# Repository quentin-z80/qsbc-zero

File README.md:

# qsbc-zero

## About

Specs:

- i.MX6ULL ARM Cortex-A7
- 512MB DDR3L
- 4MB QSPI Flash
- MicroSD card slot
- USB Type-C DRP and USB Type-A port
- 10/100M Ethernet
- Dual 36 pin GPIO headers
- PF1510 PMIC
- USB Type-C Power in

Manufactured using JLCPCB's JLC2116 stackup

## Setup

### Flashing u-boot

  1. Build `imx_usb_loader`

        ```
        git clone git@github.com:boundarydevices/imx_usb_loader.git
        cd imx_usb_loader
        make
        ```

  2. Build `u-boot`

        ```
        git clone git@gitlab.com:quentin-z80/u-boot.git
        cd u-boot
        export CROSS_COMPILE=arm-linux-gnueabi- ARCH=arm
        make qsbc-zero_defconfig
        make
        ```

  3. Build `qspi-header`

        ```
        cd tools/qspi-header
        ./qspi-header.sh qspi-nor-winbond-w25q32jv-config qspi-config.bin
        ```

  4. Connect to board over serial and load `u-boot` over usb

        ```
        screen /dev/ttyUSB0 115200
        ./imx_usb_loader /path/to/u-boot/u-boot-dtb.imx
        ```

  5. Transfer `qspi-header` over XMODEM or any other method and flash

        ```
        sf probe
        sf erase 0x0 0x400000
        loadx
        ```

        in screen hit `Ctrl-A` followed by `:`

        ```
        exec !! sx /path/to/qspi-header/qspi-config.bin
        sf write $loadaddr 0x400 $filesize
        ```

  6. Transfer `u-boot` over XMODEM or any other method and flash

        ```
        loadx
        ```

        in screen hit `Ctrl-A` followed by `:`

        ```
        exec !! sx /path/to/u-boot/u-boot-dtb.imx
        sf write $loadaddr 0x1000 $filesize
        ```

  7. Blow fuses to boot from qspi

        ```
        fuse prog -y 0 5 0x10 #BOOT_CFG1[4] = 1
        fuse prog -y 0 6 0x10 #BT_FUSE_SEL = 1
        ```

## TODO

### Rev 3
- Use interrupt for ETH PHY
- Swap USB-A and USB-C Locations
- Change SOC power tracks to zones

### Linux
- Port PF1510 driver

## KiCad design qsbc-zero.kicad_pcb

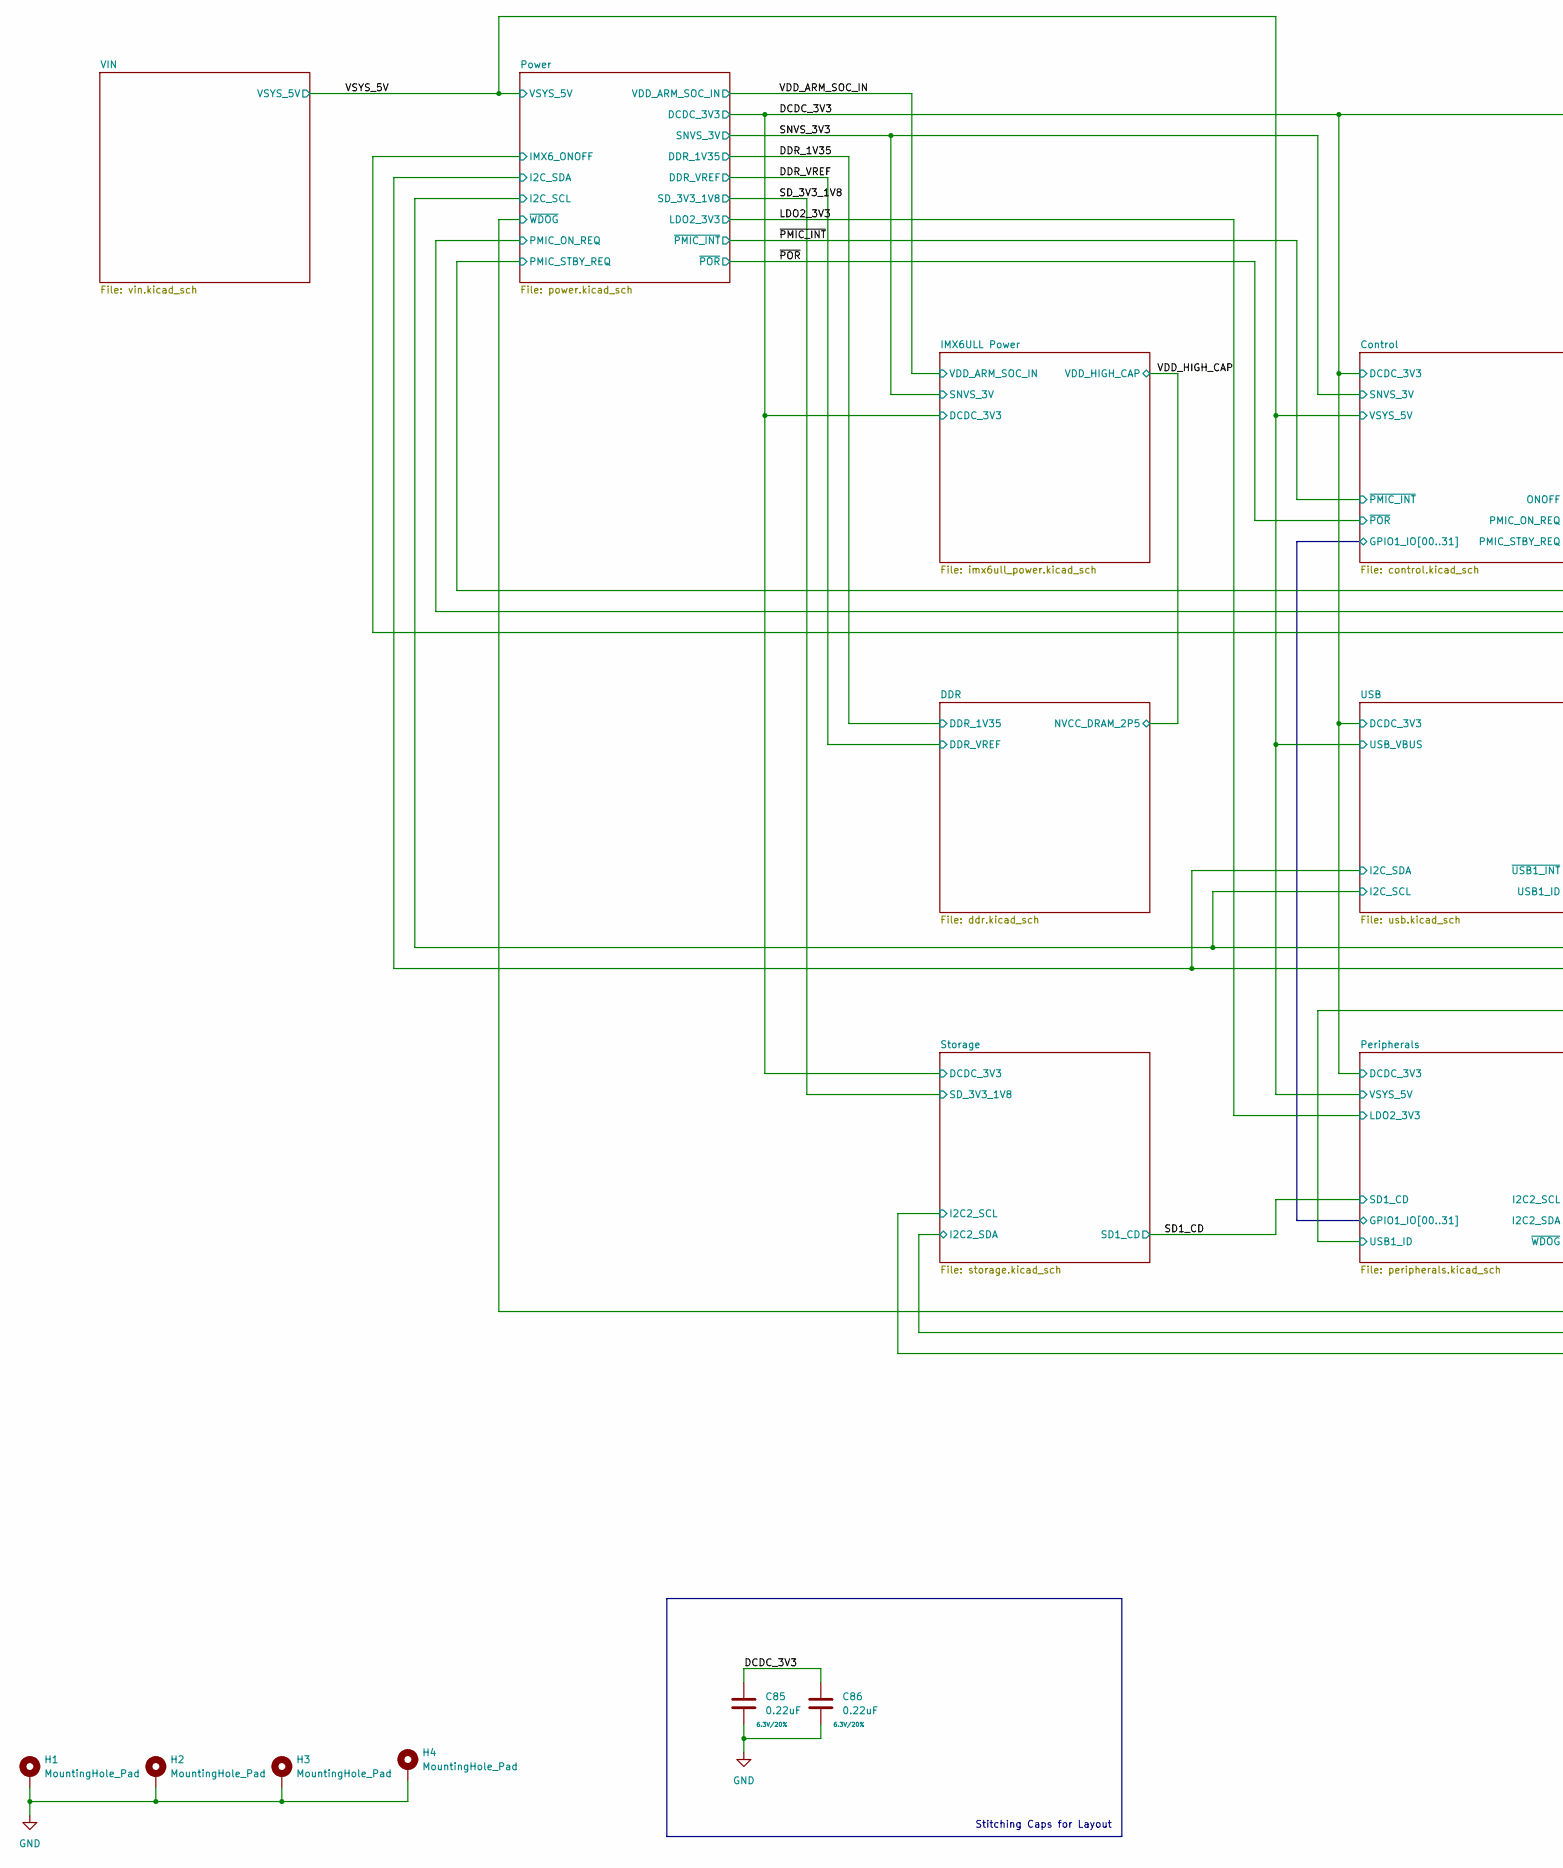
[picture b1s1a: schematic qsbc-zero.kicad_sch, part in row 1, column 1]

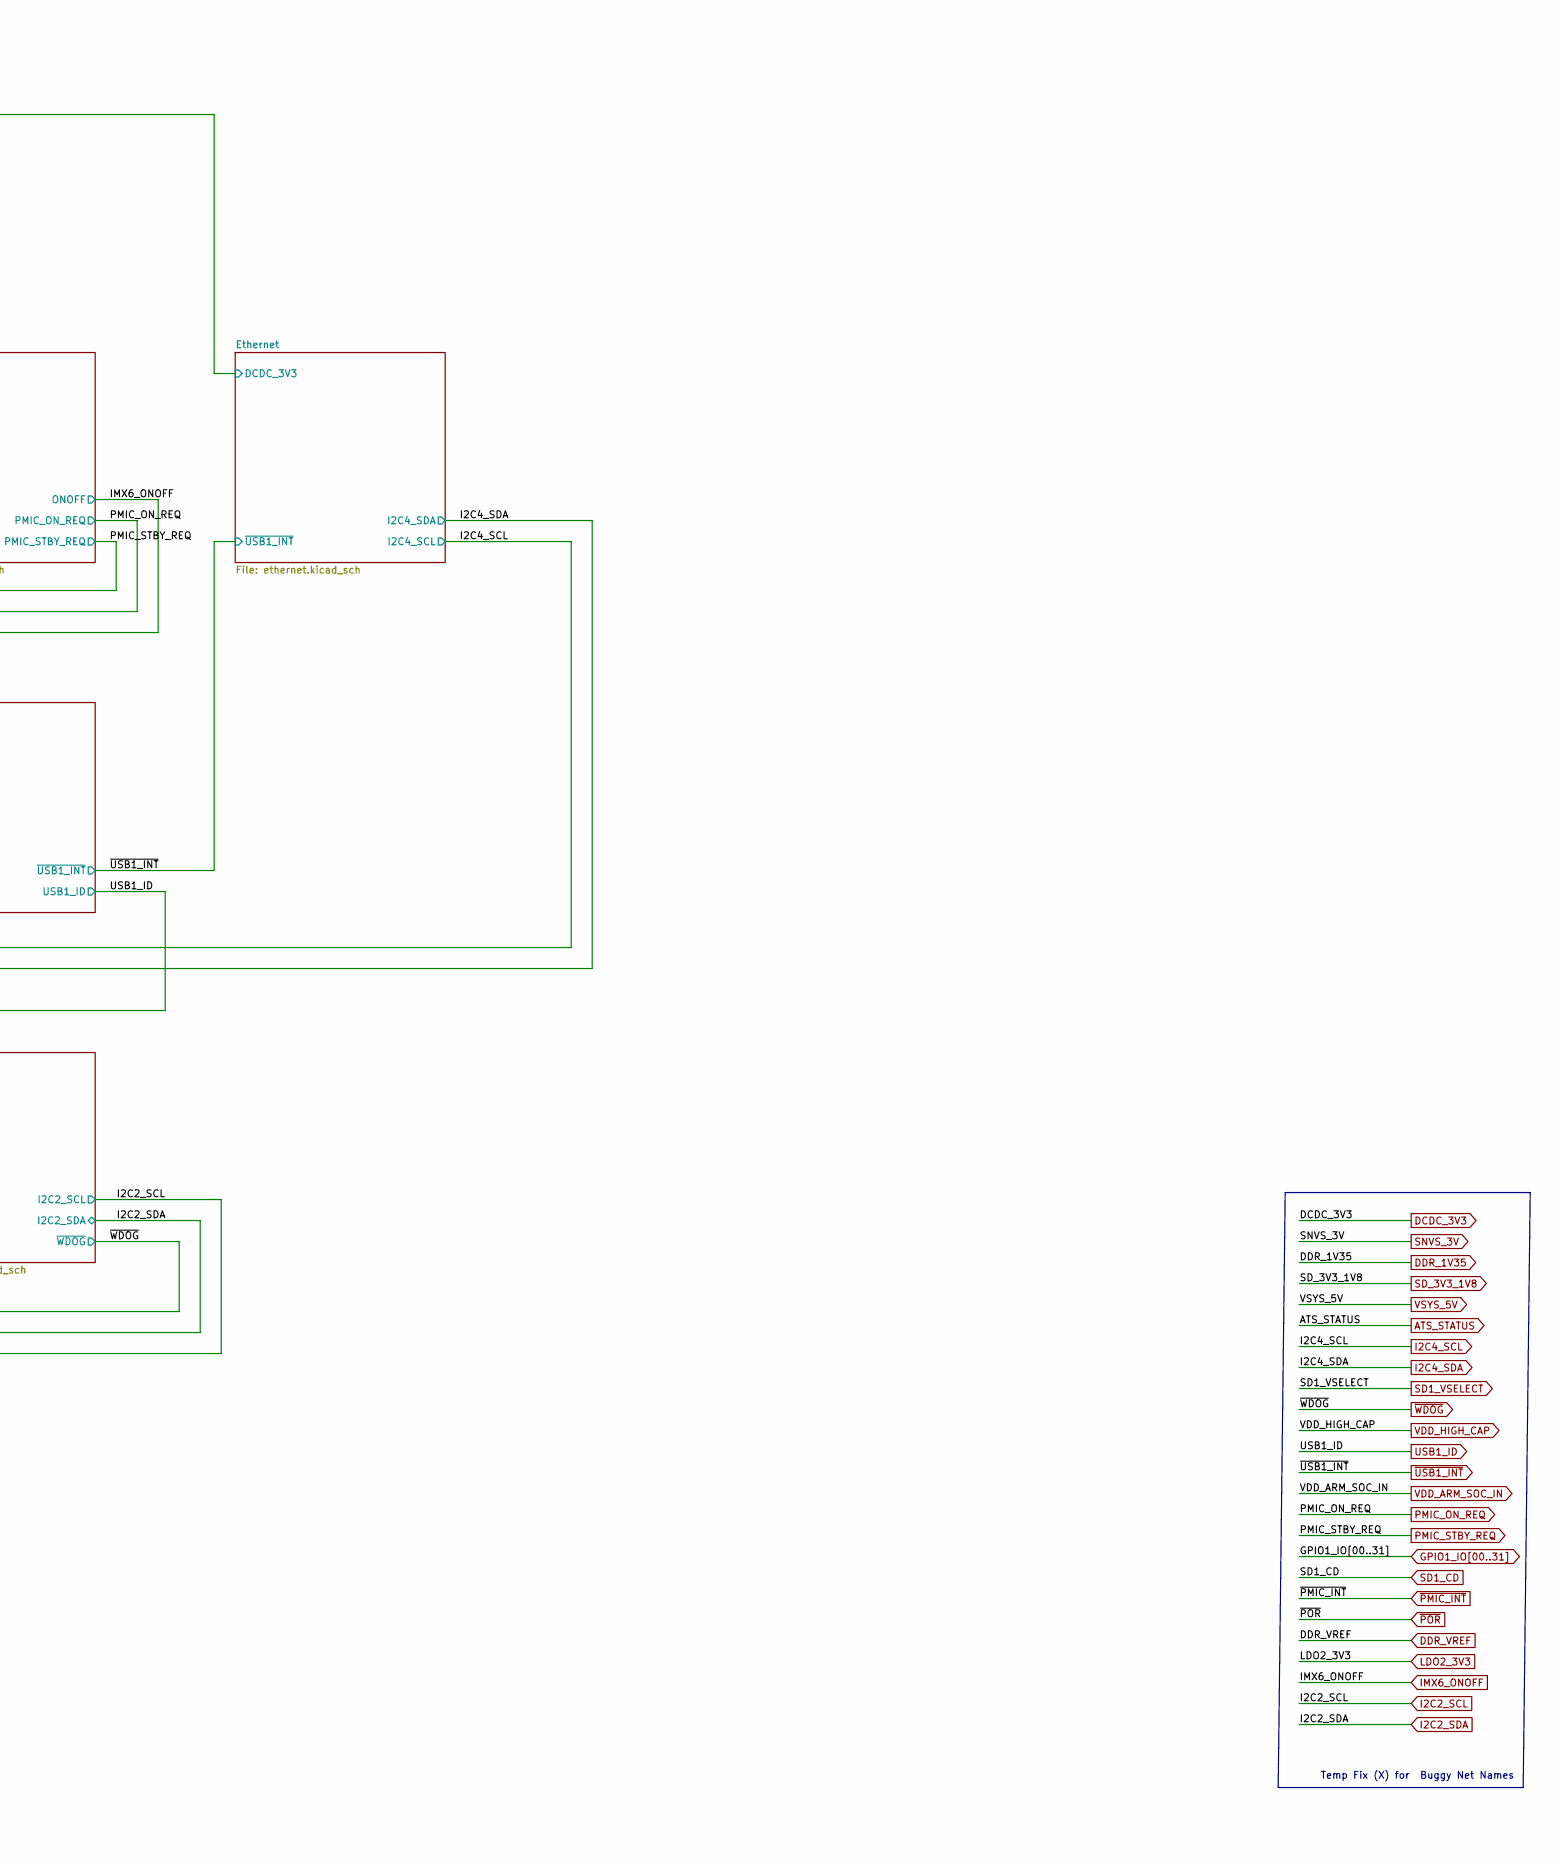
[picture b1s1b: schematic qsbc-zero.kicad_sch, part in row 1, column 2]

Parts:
C85, C86: 0.22uF; C_0201_0603Metric; Rating 6.3V/20%; MPN GRM033C80J224KE90D; DigiKey_PN 490-10392-1-ND
H1, H2, H3, H4: MountingHole_Pad; MountingHole_3.2mm_M3_Pad_Via

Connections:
DCDC_3V3: C85.1, C86.1; also elsewhere on the board
GND: C85.2, C86.2, H1.1, H2.1, H3.1, H4.1; also elsewhere on the board

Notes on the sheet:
Stitching Caps for Layout
Temp Fix (X) for Buggy Net Names

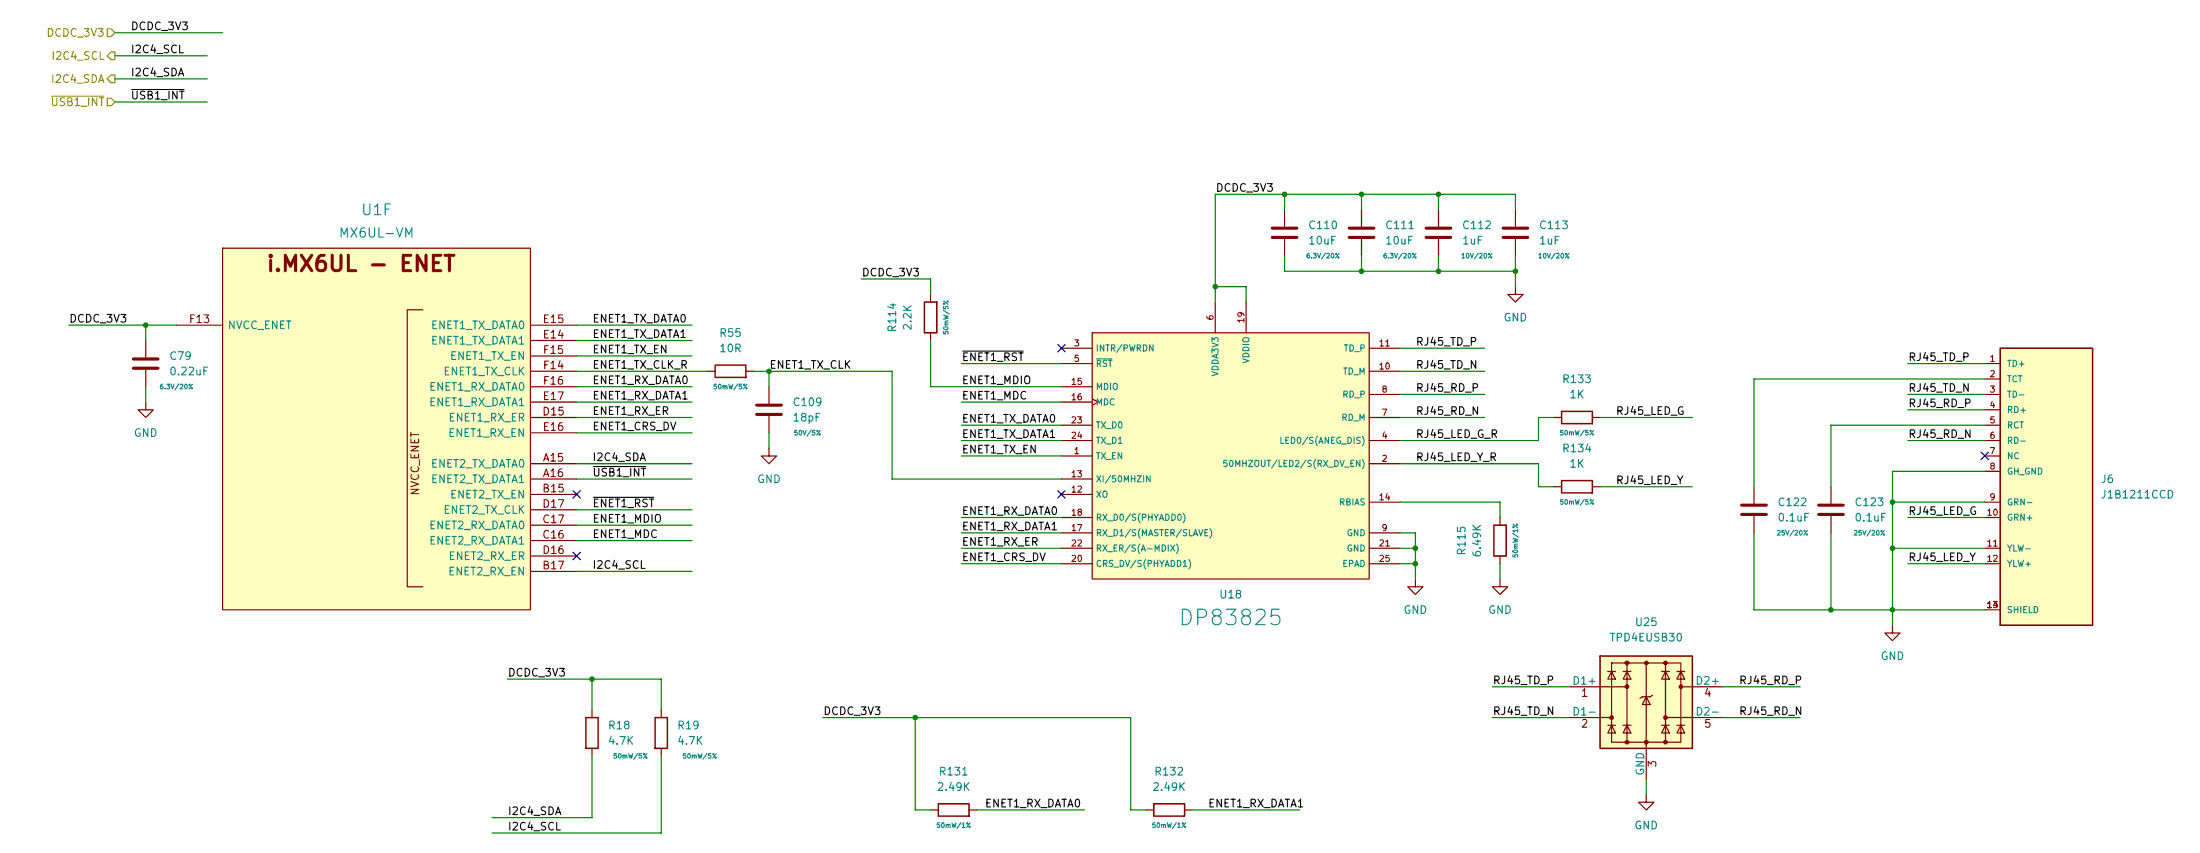
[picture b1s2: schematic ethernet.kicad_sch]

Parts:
C79: 0.22uF; C_0201_0603Metric; Rating 6.3V/20%; MPN GRM033C80J224KE90D; DigiKey_PN 490-10392-1-ND
C109: 18pF; C_0402_1005Metric; Rating 50V/5%; MPN CC0402JRNPO9BN180; DigiKey_PN 311-1415-1-ND
C110, C111: 10uF; C_0402_1005Metric; Rating 6.3V/20%; MPN GRM155R60J106ME05D; DigiKey_PN 490-GRM155R60J106ME05DCT-ND
C112, C113: 1uF; C_0402_1005Metric; Rating 10V/20%; MPN GCM155C71A105KE38D; DigiKey_PN 490-13409-1-ND
C122, C123: 0.1uF; C_0402_1005Metric; Rating 25V/20%; MPN GRM155R71E104KE14J; DigiKey_PN 490-14603-1-ND
J6: J1B1211CCD; MPN J1B1211CCD; DigiKey_PN 1278-1052-ND
R18, R19: 4.7K; R_0402_1005Metric; Rating 50mW/5%; MPN RC0402JR-074K7L; DigiKey_PN 311-4.7KJRCT-ND
R55: 10R; R_0402_1005Metric; Rating 50mW/5%; MPN RC0402JR-0710RL; DigiKey_PN 311-10JRCT-ND
R114: 2.2K; R_0402_1005Metric; Rating 50mW/5%; MPN RC0402JR-072K2L; DigiKey_PN 311-2.2KJRCT-ND
R115: 6.49K; R_0402_1005Metric; Rating 50mW/1%; MPN RC0402FR-076K49L; DigiKey_PN 311-6.49KLRCT-ND
R131, R132: 2.49K; R_0402_1005Metric; Rating 50mW/1%; MPN RC0402FR-072K49L; DigiKey_PN 311-2.49KLRCT-ND
R133, R134: 1K; R_0402_1005Metric; Rating 50mW/5%; MPN RC0402JR-071KL; DigiKey_PN 311-1.0KJRCT-ND
U1: MX6UL-VM; SOT1534-2; MPN MCIMX6Y2DVM09AB; DigiKey_PN 568-14995-ND
U18: DP83825; XCVR_DP83825IRMQR; MPN DP83825IRMQR; DigiKey_PN 296-DP83825IRMQRCT-ND
U25: TPD4EUSB30; USON-10_2.5x1.0mm_P0.5mm; MPN TPD4EUSB30DQAR; DigiKey_PN 296-28063-1-ND

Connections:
/Ethernet/ENET1_CRS_DV: U1.E16 (ENET1_RX_EN), U18.20 (CRS_DV/S(PHYADD1))
/Ethernet/ENET1_MDC: U1.C16 (ENET2_RX_DATA1), U18.16 (MDC)
/Ethernet/ENET1_MDIO: R114.1, U1.C17 (ENET2_RX_DATA0), U18.15 (MDIO)
/Ethernet/ENET1_RX_DATA0: R131.2, U1.F16 (ENET1_RX_DATA0), U18.18 (RX_D0/S(PHYADD0))
/Ethernet/ENET1_RX_DATA1: R132.2, U1.E17 (ENET1_RX_DATA1), U18.17 (RX_D1/S(MASTER/SLAVE))
/Ethernet/ENET1_RX_ER: U1.D15 (ENET1_RX_ER), U18.22 (RX_ER/S(A-MDIX))
/Ethernet/ENET1_TX_CLK: C109.1, R55.2, U18.13 (XI/50MHZIN)
/Ethernet/ENET1_TX_CLK_R: R55.1, U1.F14 (ENET1_TX_CLK)
/Ethernet/ENET1_TX_DATA0: U1.E15 (ENET1_TX_DATA0), U18.23 (TX_D0)
/Ethernet/ENET1_TX_DATA1: U1.E14 (ENET1_TX_DATA1), U18.24 (TX_D1)
/Ethernet/ENET1_TX_EN: U1.F15 (ENET1_TX_EN), U18.1 (TX_EN)
/Ethernet/RJ45_LED_G: J6.10 (GRN+), R133.2
/Ethernet/RJ45_LED_G_R: R133.1, U18.4 (LED0/S(ANEG_DIS))
/Ethernet/RJ45_LED_Y: J6.12 (YLW+), R134.2
/Ethernet/RJ45_LED_Y_R: R134.1, U18.2 (50MHZOUT/LED2/S(RX_DV_EN))
/Ethernet/RJ45_RD_N: J6.6 (RD-), U18.7 (RD_M), U25.5 (D2-), U25.6
/Ethernet/RJ45_RD_P: J6.4 (RD+), U18.8 (RD_P), U25.4 (D2+), U25.7
/Ethernet/RJ45_TD_N: J6.3 (TD-), U18.10 (TD_M), U25.2 (D1-), U25.9
/Ethernet/RJ45_TD_P: J6.1 (TD+), U18.11 (TD_P), U25.1 (D1+), U25.10
/Ethernet/~ENET1_RST: U1.D17 (ENET2_TX_CLK), U18.5 (~RST)
DCDC_3V3: C79.1, C110.1, C111.1, C112.1, C113.1, R18.1, R19.1, R114.2, R131.1, R132.1, U1.F13 (NVCC_ENET), U18.6 (VDDA3V3), U18.19 (VDDIO); also elsewhere on the board
GND: C79.2, C109.2, C110.2, C111.2, C112.2, C113.2, C122.2, C123.2, J6.8 (GH_GND), J6.9 (GRN-), J6.11 (YLW-), J6.13 (SHIELD), J6.14 (SHIELD), R115.1, U18.9 (GND), U18.21 (GND), U18.25 (EPAD), U18.26 (EPAD), U18.27 (EPAD), U18.28 (EPAD), U18.29 (EPAD), U18.30 (EPAD), U25.3 (GND), U25.8 (GND); also elsewhere on the board
I2C4_SCL: R19.2, U1.B17 (ENET2_RX_EN); also elsewhere on the board
I2C4_SDA: R18.2, U1.A15 (ENET2_TX_DATA0); also elsewhere on the board
unnamed: C122.1, J6.2 (TCT)
unnamed: C123.1, J6.5 (RCT)
unnamed: R115.2, U18.14 (RBIAS)
~USB1_INT: U1.A16 (ENET2_TX_DATA1); also elsewhere on the board

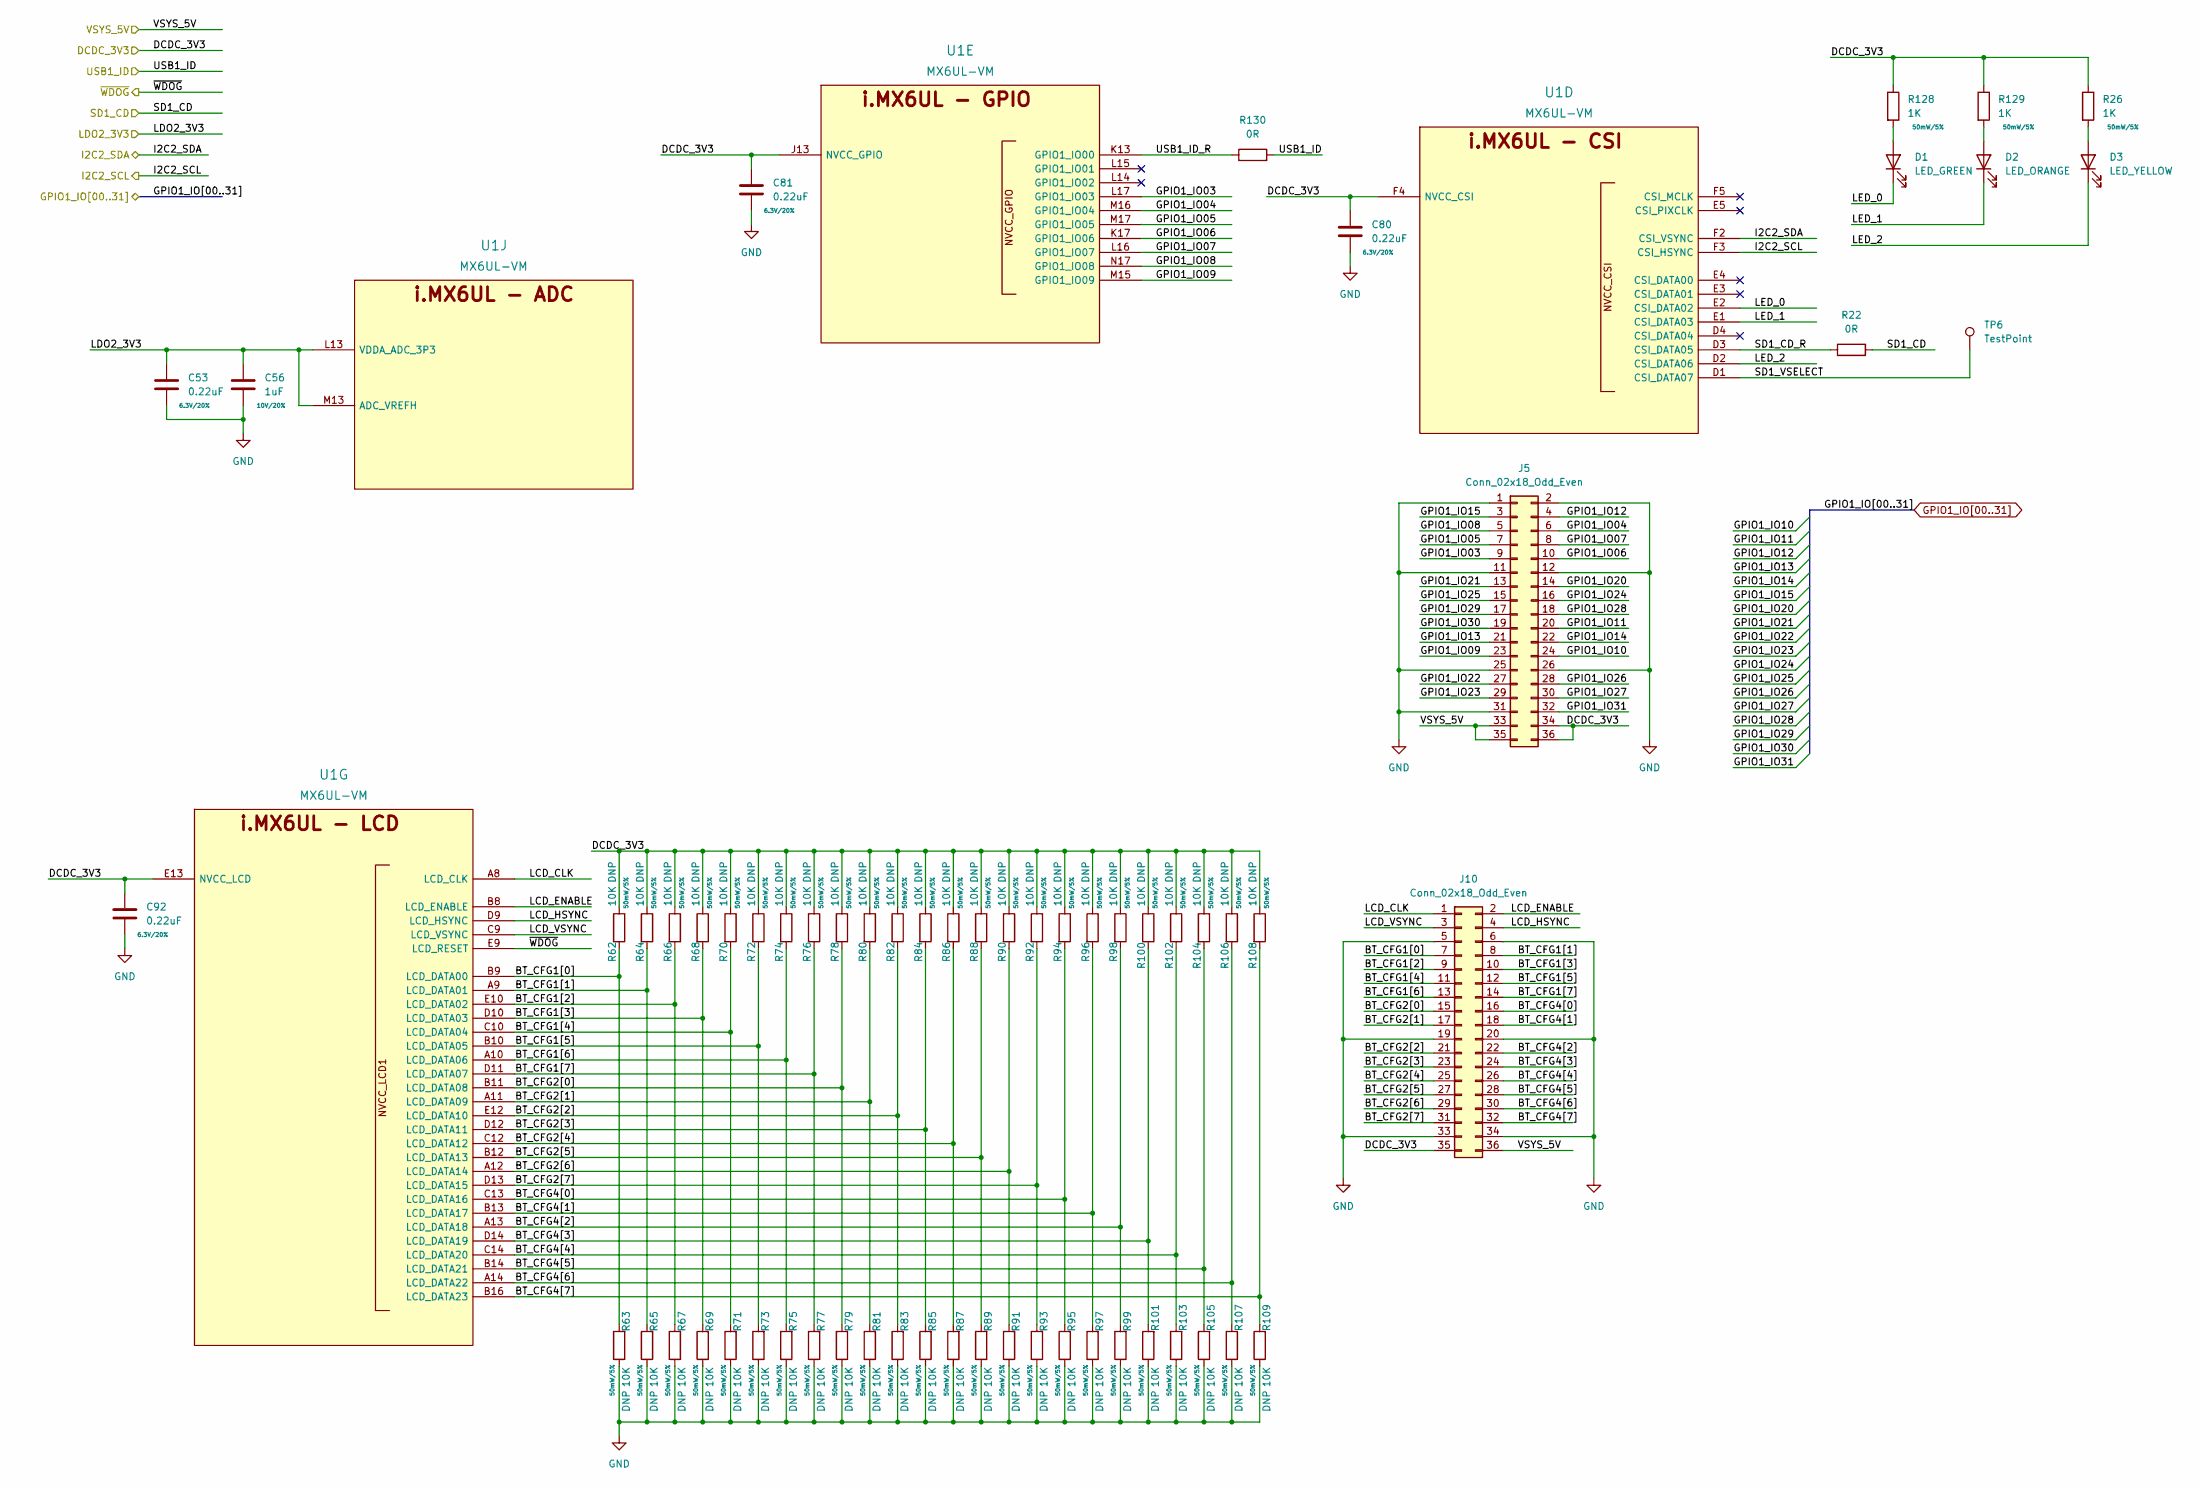
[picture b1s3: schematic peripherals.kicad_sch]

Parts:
C53, C80, C81, C92: 0.22uF; C_0201_0603Metric; Rating 6.3V/20%; MPN GRM033C80J224KE90D; DigiKey_PN 490-10392-1-ND
C56: 1uF; C_0402_1005Metric; Rating 10V/20%; MPN GCM155C71A105KE38D; DigiKey_PN 490-13409-1-ND
D1: LED_GREEN; LED_0603_1608Metric; MPN SML-D12M8WT86; DigiKey_PN 511-1578-1-ND
D2: LED_ORANGE; LED_0603_1608Metric; MPN SML-E12D8WT86; DigiKey_PN 511-1583-1-ND
D3: LED_YELLOW; LED_0603_1608Metric; MPN SML-E12Y8WT86; DigiKey_PN 511-1588-1-ND
J5, J10: Conn_02x18_Odd_Even; PinHeader_2x18_P2.54mm_Vertical; MPN PRPC018DAAN-RC; DigiKey_PN S2011EC-18-ND
R22, R130: 0R; R_0402_1005Metric; MPN RC0402FR-070RL; DigiKey_PN 311-0.0LRCT-ND
R26, R128, R129: 1K; R_0402_1005Metric; Rating 50mW/5%; MPN RC0402JR-071KL; DigiKey_PN 311-1.0KJRCT-ND
R62, R63, R64, R65, R66, R67, R68, R69, R70, R71, R72, R73, R74, R75, R76, R77, R78, R79, R80, R81, R82, R83, R84, R85, R86, R87, R88, R89, R90, R91, R92, R93, R94, R95, R96, R97, R98, R99, R100, R101, R102, R103, R104, R105, R106, R107, R108, R109: 10K; R_0402_1005Metric; Rating 50mW/5%; MPN RC0402JR-0710KL; DigiKey_PN 311-10KJRCT-ND
TP6: TestPoint; TestPoint_Pad_D1.0mm
U1: MX6UL-VM; SOT1534-2; MPN MCIMX6Y2DVM09AB; DigiKey_PN 568-14995-ND

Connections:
/Peripherals/BT_CFG1[0]: J10.7, R62.2, R63.2, U1.B9 (LCD_DATA00)
/Peripherals/BT_CFG1[1]: J10.8, R64.2, R65.2, U1.A9 (LCD_DATA01)
/Peripherals/BT_CFG1[2]: J10.9, R66.2, R67.2, U1.E10 (LCD_DATA02)
/Peripherals/BT_CFG1[3]: J10.10, R68.2, R69.2, U1.D10 (LCD_DATA03)
/Peripherals/BT_CFG1[4]: J10.11, R70.2, R71.2, U1.C10 (LCD_DATA04)
/Peripherals/BT_CFG1[5]: J10.12, R72.2, R73.2, U1.B10 (LCD_DATA05)
/Peripherals/BT_CFG1[6]: J10.13, R74.2, R75.2, U1.A10 (LCD_DATA06)
/Peripherals/BT_CFG1[7]: J10.14, R76.2, R77.2, U1.D11 (LCD_DATA07)
/Peripherals/BT_CFG2[0]: J10.15, R78.2, R79.2, U1.B11 (LCD_DATA08)
/Peripherals/BT_CFG2[1]: J10.17, R80.2, R81.2, U1.A11 (LCD_DATA09)
/Peripherals/BT_CFG2[2]: J10.21, R82.2, R83.2, U1.E12 (LCD_DATA10)
/Peripherals/BT_CFG2[3]: J10.23, R84.2, R85.2, U1.D12 (LCD_DATA11)
/Peripherals/BT_CFG2[4]: J10.25, R86.2, R87.2, U1.C12 (LCD_DATA12)
/Peripherals/BT_CFG2[5]: J10.27, R88.2, R89.2, U1.B12 (LCD_DATA13)
/Peripherals/BT_CFG2[6]: J10.29, R90.2, R91.2, U1.A12 (LCD_DATA14)
/Peripherals/BT_CFG2[7]: J10.31, R92.2, R93.2, U1.D13 (LCD_DATA15)
/Peripherals/BT_CFG4[0]: J10.16, R94.2, R95.2, U1.C13 (LCD_DATA16)
/Peripherals/BT_CFG4[1]: J10.18, R96.2, R97.2, U1.B13 (LCD_DATA17)
/Peripherals/BT_CFG4[2]: J10.22, R98.2, R99.2, U1.A13 (LCD_DATA18)
/Peripherals/BT_CFG4[3]: J10.24, R100.2, R101.2, U1.D14 (LCD_DATA19)
/Peripherals/BT_CFG4[4]: J10.26, R102.2, R103.2, U1.C14 (LCD_DATA20)
/Peripherals/BT_CFG4[5]: J10.28, R104.2, R105.2, U1.B14 (LCD_DATA21)
/Peripherals/BT_CFG4[6]: J10.30, R106.2, R107.2, U1.A14 (LCD_DATA22)
/Peripherals/BT_CFG4[7]: J10.32, R108.2, R109.2, U1.B16 (LCD_DATA23)
/Peripherals/GPIO1_IO03: J5.9, U1.L17 (GPIO1_IO03)
/Peripherals/GPIO1_IO04: J5.6, U1.M16 (GPIO1_IO04)
/Peripherals/GPIO1_IO05: J5.7, U1.M17 (GPIO1_IO05)
/Peripherals/GPIO1_IO06: J5.10, U1.K17 (GPIO1_IO06)
/Peripherals/GPIO1_IO07: J5.8, U1.L16 (GPIO1_IO07)
/Peripherals/GPIO1_IO08: J5.5, U1.N17 (GPIO1_IO08)
/Peripherals/GPIO1_IO09: J5.23, U1.M15 (GPIO1_IO09)
/Peripherals/LCD_CLK: J10.1, U1.A8 (LCD_CLK)
/Peripherals/LCD_ENABLE: J10.2, U1.B8 (LCD_ENABLE)
/Peripherals/LCD_HSYNC: J10.4, U1.D9 (LCD_HSYNC)
/Peripherals/LCD_VSYNC: J10.3, U1.C9 (LCD_VSYNC)
/Peripherals/LED_0: D1.1 (K), U1.E2 (CSI_DATA02)
/Peripherals/LED_1: D2.1 (K), U1.E1 (CSI_DATA03)
/Peripherals/LED_2: D3.1 (K), U1.D2 (CSI_DATA06)
/Peripherals/SD1_CD_R: R22.1, U1.D3 (CSI_DATA05)
/Peripherals/SD1_VSELECT: TP6.1, U1.D1 (CSI_DATA07)
/Peripherals/USB1_ID_R: R130.1, U1.K13 (GPIO1_IO00)
DCDC_3V3: C80.1, C81.1, C92.1, J5.34, J5.36, J10.35, R26.1, R62.1, R64.1, R66.1, R68.1, R70.1, R72.1, R74.1, R76.1, R78.1, R80.1, R82.1, R84.1, R86.1, R88.1, R90.1, R92.1, R94.1, R96.1, R98.1, R100.1, R102.1, R104.1, R106.1, R108.1, R128.1, R129.1, U1.E13 (NVCC_LCD), U1.F4 (NVCC_CSI), U1.J13 (NVCC_GPIO); also elsewhere on the board
GND: C53.2, C56.2, C80.2, C81.2, C92.2, J5.1, J5.2, J5.11, J5.12, J5.25, J5.26, J5.31, J10.5, J10.6, J10.19, J10.20, J10.33, J10.34, R63.1, R65.1, R67.1, R69.1, R71.1, R73.1, R75.1, R77.1, R79.1, R81.1, R83.1, R85.1, R87.1, R89.1, R91.1, R93.1, R95.1, R97.1, R99.1, R101.1, R103.1, R105.1, R107.1, R109.1; also elsewhere on the board
GPIO1_IO10: J5.24; also elsewhere on the board
GPIO1_IO11: J5.20; also elsewhere on the board
GPIO1_IO12: J5.4; also elsewhere on the board
GPIO1_IO13: J5.21; also elsewhere on the board
GPIO1_IO14: J5.22; also elsewhere on the board
GPIO1_IO15: J5.3; also elsewhere on the board
GPIO1_IO20: J5.14; also elsewhere on the board
GPIO1_IO21: J5.13; also elsewhere on the board
GPIO1_IO22: J5.27; also elsewhere on the board
GPIO1_IO23: J5.29; also elsewhere on the board
GPIO1_IO24: J5.16; also elsewhere on the board
GPIO1_IO25: J5.15; also elsewhere on the board
GPIO1_IO26: J5.28; also elsewhere on the board
GPIO1_IO27: J5.30; also elsewhere on the board
GPIO1_IO28: J5.18; also elsewhere on the board
GPIO1_IO29: J5.17; also elsewhere on the board
GPIO1_IO30: J5.19; also elsewhere on the board
GPIO1_IO31: J5.32; also elsewhere on the board
I2C2_SCL: U1.F3 (CSI_HSYNC); also elsewhere on the board
I2C2_SDA: U1.F2 (CSI_VSYNC); also elsewhere on the board
LDO2_3V3: C53.1, C56.1, U1.L13 (VDDA_ADC_3P3), U1.M13 (ADC_VREFH); also elsewhere on the board
unnamed: D1.2 (A), R128.2
unnamed: D2.2 (A), R129.2
unnamed: D3.2 (A), R26.2
SD1_CD: R22.2; also elsewhere on the board
USB1_ID: R130.2; also elsewhere on the board
VSYS_5V: J5.33, J5.35, J10.36; also elsewhere on the board
~WDOG: U1.E9 (LCD_RESET); also elsewhere on the board

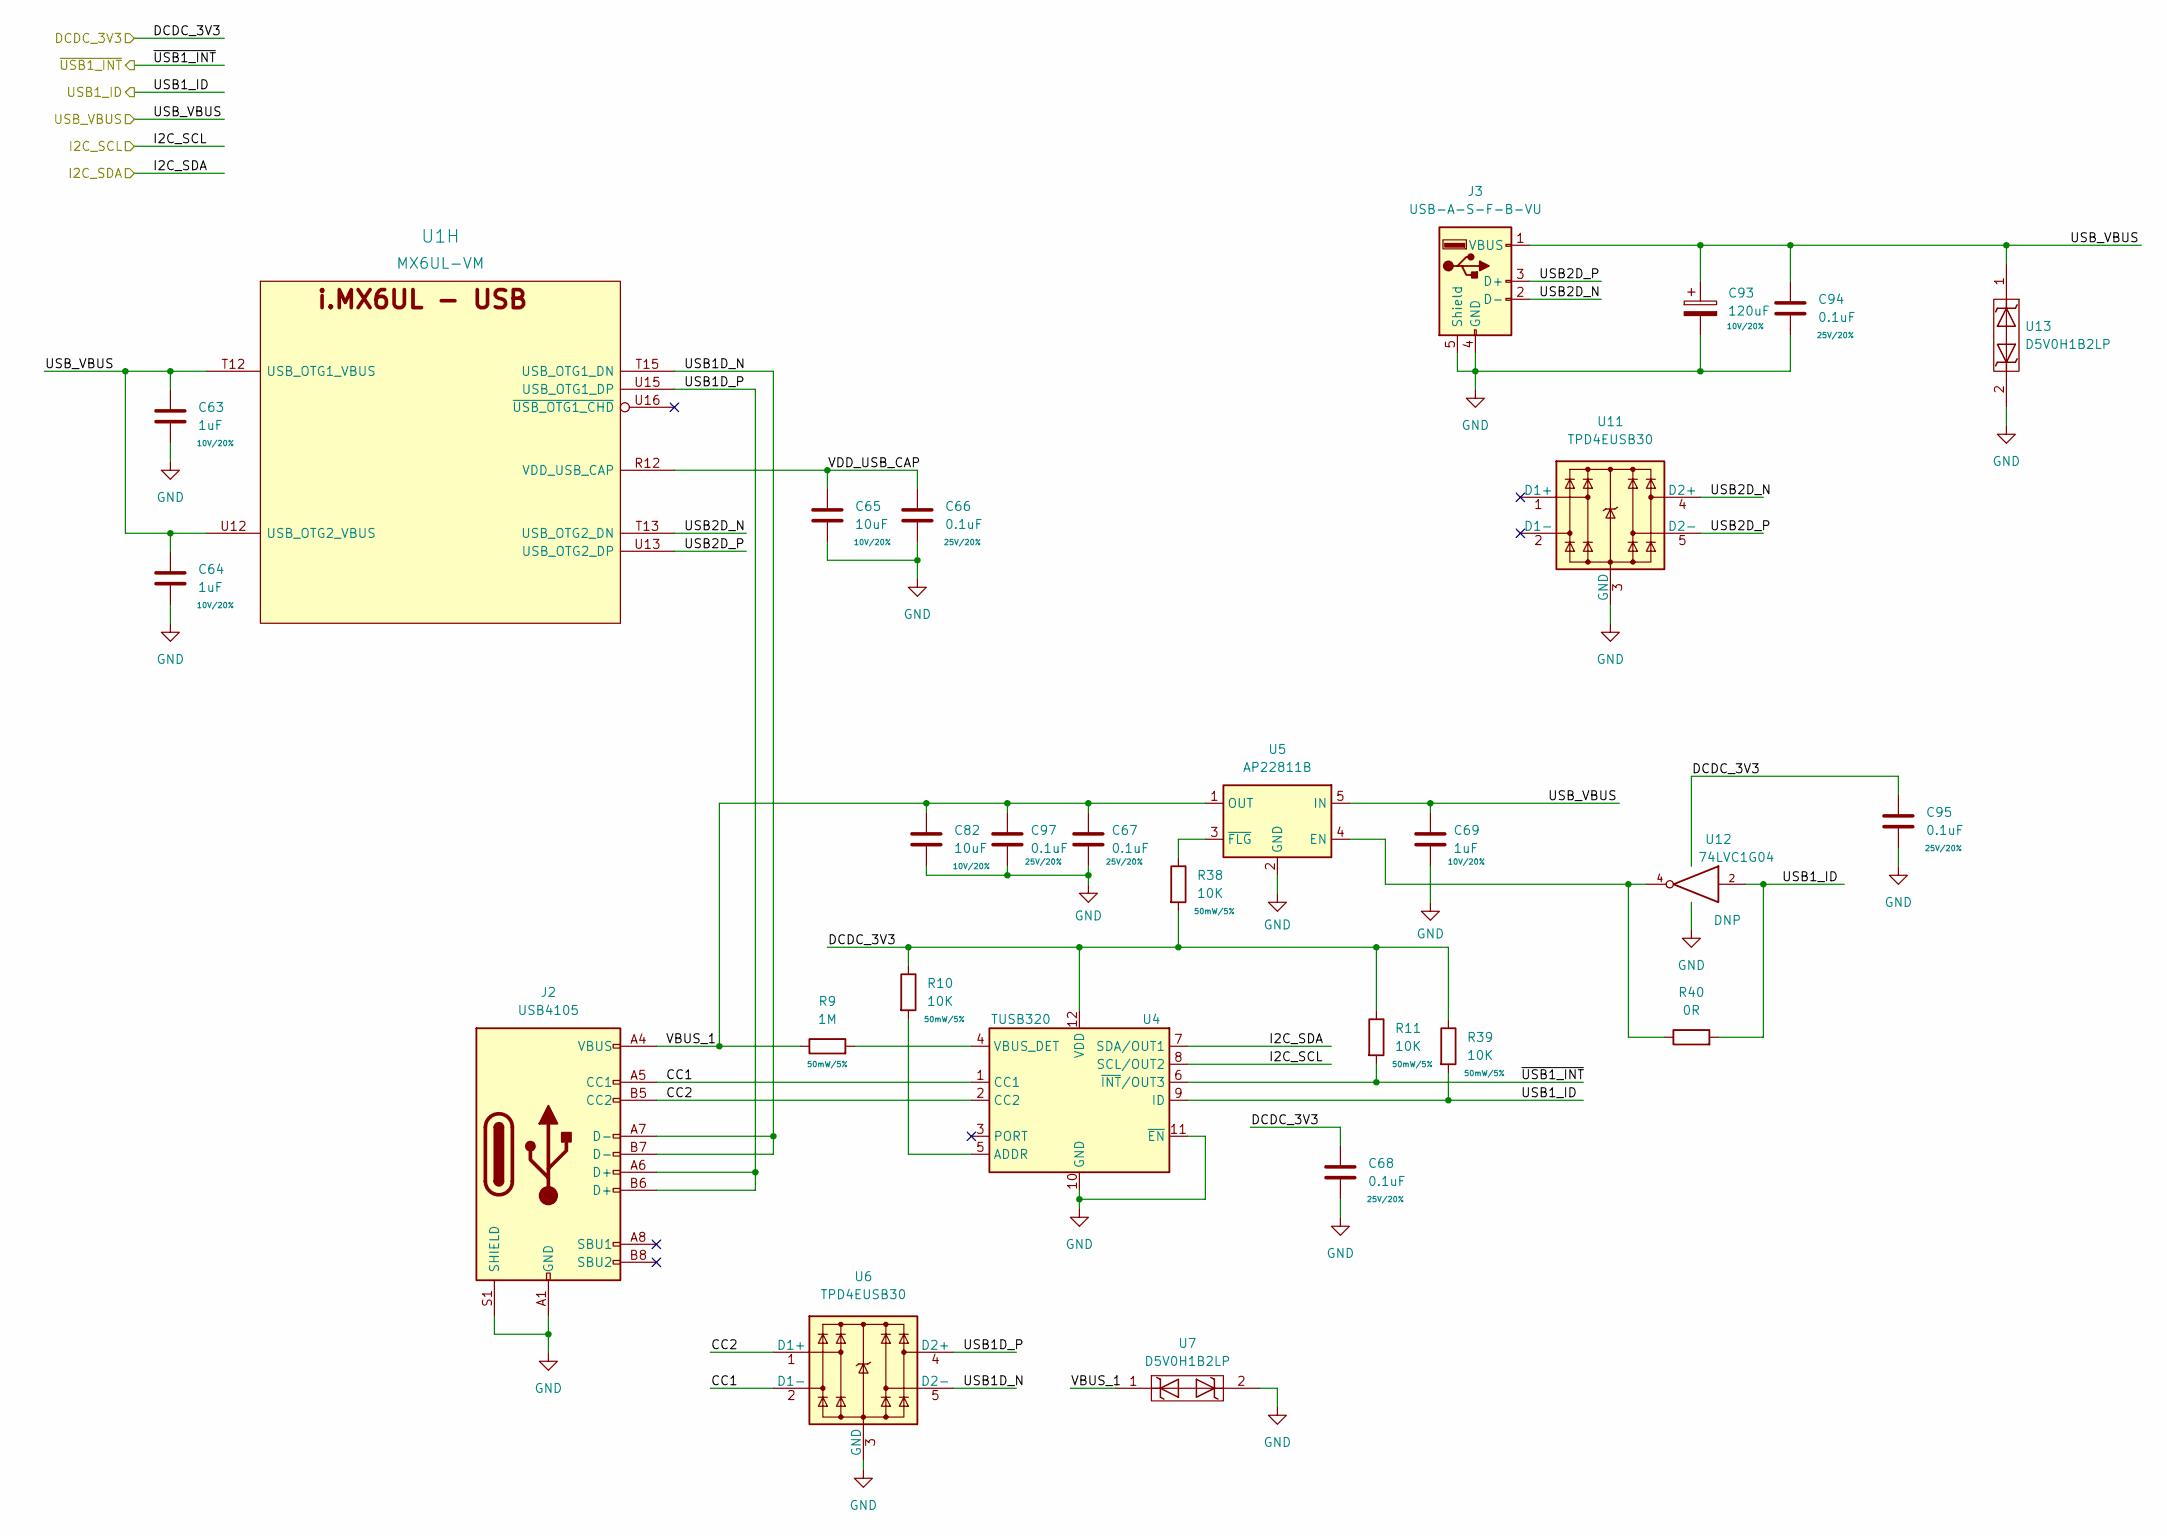
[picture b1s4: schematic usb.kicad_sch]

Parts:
C63, C64, C69: 1uF; C_0402_1005Metric; Rating 10V/20%; MPN GCM155C71A105KE38D; DigiKey_PN 490-13409-1-ND
C65, C82: 10uF; C_0402_1005Metric; Rating 10V/20%; MPN CL05A106MP5NUNC; DigiKey_PN 1276-1450-1-ND
C66, C67, C68, C94, C95, C97: 0.1uF; C_0402_1005Metric; Rating 25V/20%; MPN GRM155R71E104KE14J; DigiKey_PN 490-14603-1-ND
C93: 120uF; CP_Elec_6.3x4.9; Rating 10V/20%; MPN 875105244013; DigiKey_PN 732-6413-1-ND
J2: USB4105; USB_C_Receptacle_HRO_TYPE-C-31-M-12; MPN USB4105-GF-A; DigiKey_PN 2073-USB4105-GF-ACT-ND
J3: USB-A-S-F-B-VU; SAMTEC_USB-A-S-X-X-VU; MPN USB-A-S-F-B-VU; DigiKey_PN SAM10862-ND
R9: 1M; R_0402_1005Metric; Rating 50mW/5%; MPN RC0402JR-071ML; DigiKey_PN 311-1.0MJRCT-ND
R10, R11, R38, R39: 10K; R_0402_1005Metric; Rating 50mW/5%; MPN RC0402JR-0710KL; DigiKey_PN 311-10KJRCT-ND
R40: 0R; R_0402_1005Metric; MPN RC0402FR-070RL; DigiKey_PN 311-0.0LRCT-ND
U1: MX6UL-VM; SOT1534-2; MPN MCIMX6Y2DVM09AB; DigiKey_PN 568-14995-ND
U4: TUSB320; Texas_X2QFN-12_1.6x1.6mm_P0.4mm; MPN TUSB320LAIRWBR; DigiKey_PN 296-43142-1-ND
U5: AP22811B; SOT-23-5; MPN AP22811BW5-7; DigiKey_PN AP22811BW5-7DICT-ND
U6, U11: TPD4EUSB30; USON-10_2.5x1.0mm_P0.5mm; MPN TPD4EUSB30DQAR; DigiKey_PN 296-28063-1-ND
U7, U13: D5V0H1B2LP; DFN100X60X45-2N; MPN D5V0H1B2LP-7B; DigiKey_PN D5V0H1B2LP-7BDICT-ND
U12: 74LVC1G04; SOT-23-5; MPN SN74LVC1G04DBVR; DigiKey_PN 296-11599-1-ND

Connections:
/USB/CC1: J2.A5 (CC1), U4.1 (CC1), U6.2 (D1-), U6.9
/USB/CC2: J2.B5 (CC2), U4.2 (CC2), U6.1 (D1+), U6.10
/USB/USB1D_N: J2.A7 (D-), J2.B7 (D-), U1.T15 (USB_OTG1_DN), U6.5 (D2-), U6.6
/USB/USB1D_P: J2.A6 (D+), J2.B6 (D+), U1.U15 (USB_OTG1_DP), U6.4 (D2+), U6.7
/USB/USB2D_N: J3.2 (D-), U1.T13 (USB_OTG2_DN), U11.4 (D2+), U11.7
/USB/USB2D_P: J3.3 (D+), U1.U13 (USB_OTG2_DP), U11.5 (D2-), U11.6
/USB/VBUS_1: C67.1, C82.1, C97.1, J2.A4 (VBUS), J2.A9 (VBUS), J2.B4 (VBUS), J2.B9 (VBUS), R9.1, U5.1 (OUT), U7.1
/USB/VDD_USB_CAP: C65.1, C66.1, U1.R12 (VDD_USB_CAP)
DCDC_3V3: C68.1, C95.1, R10.1, R11.1, R38.2, R39.1, U4.12 (VDD), U12.5 (VCC); also elsewhere on the board
GND: C63.2, C64.2, C65.2, C66.2, C67.2, C68.2, C69.2, C82.2, C93.2, C94.2, C95.2, C97.2, J2.A1 (GND), J2.A12 (GND), J2.B1 (GND), J2.B12 (GND), J2.S1 (SHIELD), J3.4 (GND), J3.5 (Shield), U4.10 (GND), U4.11 (~EN), U5.2 (GND), U6.3 (GND), U6.8 (GND), U7.2, U11.3 (GND), U11.8 (GND), U12.3 (GND), U13.2; also elsewhere on the board
I2C4_SCL: U4.8 (SCL/OUT2); also elsewhere on the board
I2C4_SDA: U4.7 (SDA/OUT1); also elsewhere on the board
unnamed: R9.2, U4.4 (VBUS_DET)
unnamed: R10.2, U4.5 (ADDR)
unnamed: R38.1, U5.3 (~FLG)
unnamed: R40.1, U5.4 (EN), U12.4
USB1_ID: R39.2, R40.2, U4.9 (ID), U12.2; also elsewhere on the board
VSYS_5V: C63.1, C64.1, C69.1, C93.1, C94.1, J3.1 (VBUS), U1.T12 (USB_OTG1_VBUS), U1.U12 (USB_OTG2_VBUS), U5.5 (IN), U13.1; also elsewhere on the board
~USB1_INT: R11.2, U4.6 (~INT/OUT3); also elsewhere on the board
